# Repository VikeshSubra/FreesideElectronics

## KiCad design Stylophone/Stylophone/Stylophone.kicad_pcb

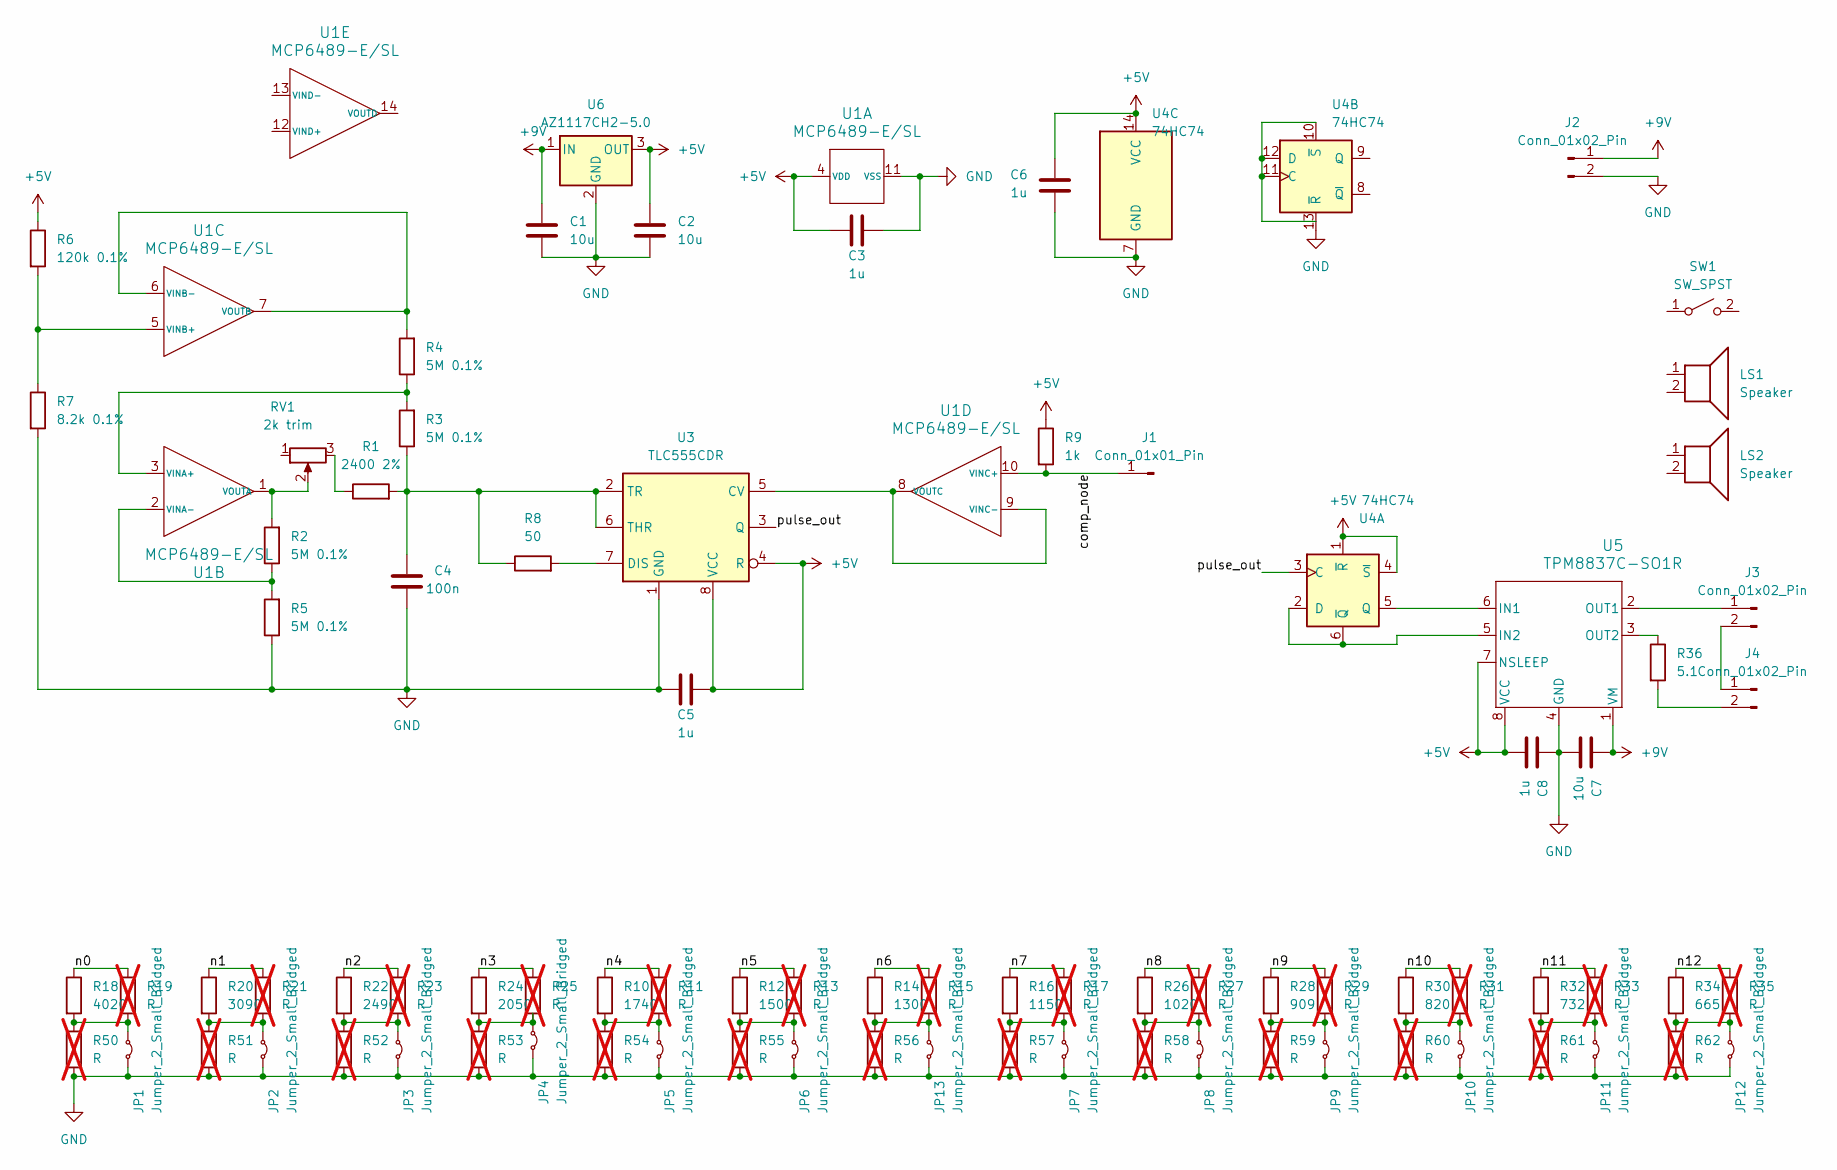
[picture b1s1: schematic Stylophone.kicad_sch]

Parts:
C1, C2, C7: 10u; C_1206_3216Metric; Part Number CL31B106KQHNFNE
C3, C5, C6, C8: 1u; C_1206_3216Metric; Part Number CL31B105KOFNNNE
C4: 100n; C_1206_3216Metric; Part Number GRM3195C1H104JA05D
J1: Conn_01x01_Pin; PinHeader_1x01_P2.54mm_Vertical
J2, J3, J4: Conn_01x02_Pin; PinHeader_1x02_P2.54mm_Vertical
JP1, JP2, JP3, JP4, JP5, JP6, JP7, JP8, JP9, JP10, JP11, JP12, JP13: Jumper_2_Small_Bridged; SolderJumper-2_P1.3mm_Bridged_RoundedPad1.0x1.5mm
LS1, LS2: Speaker; Part Number 687117740724
R1: 2400 2%; R_1206_3216Metric; Part Number RC1206FR-072K4L
R2, R3, R4, R5: 5M 0.1%; R_1206_3216Metric; Part Number RG3216P-5004-B-T1
R6: 120k 0.1%; R_1206_3216Metric; Part Number RT0805BRD07120KL
R7: 8.2k 0.1%; R_1206_3216Metric; Part Number RT0402BRD078K2L
R8: 50; R_1206_3216Metric; Part Number RC1206JR-0751RL
R9: 1k; R_1206_3216Metric
R10: 1740; R_1206_3216Metric; Part Number ERA-8AEB1741V
R11, R13, R15, R17, R19, R21, R23, R25, R27, R29, R31, R33, R35, R50, R51, R52, R53, R54, R55, R56, R57, R58, R59, R60, R61, R62: R; R_1206_3216Metric; not fitted
R12: 1500; R_1206_3216Metric; Part Number RT1206BRD071K5L
R14: 1300; R_1206_3216Metric; Part Number ERA-8AEB132V
R16: 1150; R_1206_3216Metric; Part Number RG3216P-1151-B-T5
R18: 4020; R_1206_3216Metric; Part Number ERA-8AEB4021V
R20: 3090; R_1206_3216Metric; Part Number ERA-8AEB3091V
R22: 2490; R_1206_3216Metric; Part Number RT1206BRD072K49L
R24: 2050; R_1206_3216Metric; Part Number RT1206BRD072K05L
R26: 1020; R_1206_3216Metric; Part Number ERA-8AEB1021V
R28: 909; R_1206_3216Metric; Part Number RT1206BRD07909RL
R30: 820; R_1206_3216Metric; Part Number ERA-8AEB821V
R32: 732; R_1206_3216Metric; Part Number ERA-8AEB7320V
R34: 665; R_1206_3216Metric; Part Number ERA-8AEB6650V
R36: 5.1; R_1225_3264Metric; Part Number LTR100JZPJ5R1
RV1: 2k trim; Potentiometer_Bourns_3314G_Vertical; Part Number 3314G-1-202E
SW1: SW_SPST; Part Number 016071636086
U1: MCP6489-E/SL; SOIC-14_3.9x8.7mm_P1.27mm; Part Number MCP6489-E/SL
U3: TLC555CDR; SOIC-8_3.9x4.9mm_P1.27mm; Part Number TLC555CDR
U4: 74HC74; SOIC-14_3.9x8.7mm_P1.27mm; Part Number SN74AC74DR
U5: TPM8837C-SO1R; SOIC-8_3.9x4.9mm_P1.27mm; Part Number TPM8837C-SO1R
U6: AZ1117CH2-5.0; SOT-223-3_TabPin2; Part Number AZ1117CH-5.0TRG1

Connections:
+5V: C2.1, C3.1, C5.2, C6.1, C8.2, R6.1, R9.1, U1.4 (VDD), U3.4 (R), U3.8 (VCC), U4.1 (~R), U4.4 (~S), U4.14 (VCC), U5.7 (NSLEEP), U5.8 (VCC), U6.3 (OUT)
+9V: C1.1, C7.1, J2.1, U5.1 (VM), U6.1 (IN)
/comp_node: J1.1, R9.2, U1.10 (VINC+)
/n0: R18.1, R19.1
/n1: R20.1, R21.1
/n2: R22.1, R23.1
/n3: R24.1, R25.1
/n4: R10.1, R11.1
/n5: R12.1, R13.1
/n6: R14.1, R15.1
/n7: R16.1, R17.1
/n8: R26.1, R27.1
/n9: R28.1, R29.1
/n10: R30.1, R31.1
/n11: R32.1, R33.1
/n12: R34.1, R35.1
/pulse_out: U3.3 (Q), U4.3 (C)
GND: C1.2, C2.2, C3.2, C4.1, C5.1, C6.2, C7.2, C8.1, J2.2, JP1.2 (B), JP2.2 (B), JP3.2 (B), JP4.2 (B), JP5.2 (B), JP6.2 (B), JP7.2 (B), JP8.2 (B), JP9.2 (B), JP10.2 (B), JP11.2 (B), JP12.2 (B), JP13.2 (B), R5.1, R7.2, R50.2, R51.2, R52.2, R53.2, R54.2, R55.2, R56.2, R57.2, R58.2, R59.2, R60.2, R61.2, R62.2, U1.11 (VSS), U3.1 (GND), U4.7 (GND), U4.13 (~R), U5.4 (GND), U6.2 (GND)
unnamed: J3.1, U5.2 (OUT1)
unnamed: J3.2, J4.1
unnamed: J4.2, R36.2
unnamed: JP1.1 (A), R18.2, R19.2, R50.1
unnamed: JP2.1 (A), R20.2, R21.2, R51.1
unnamed: JP3.1 (A), R22.2, R23.2, R52.1
unnamed: JP4.1 (A), R24.2, R25.2, R53.1
unnamed: JP5.1 (A), R10.2, R11.2, R54.1
unnamed: JP6.1 (A), R12.2, R13.2, R55.1
unnamed: JP7.1 (A), R16.2, R17.2, R57.1
unnamed: JP8.1 (A), R26.2, R27.2, R58.1
unnamed: JP9.1 (A), R28.2, R29.2, R59.1
unnamed: JP10.1 (A), R30.2, R31.2, R60.1
unnamed: JP11.1 (A), R32.2, R33.2, R61.1
unnamed: JP12.1 (A), R34.2, R35.2, R62.1
unnamed: JP13.1 (A), R14.2, R15.2, R56.1
unnamed: R1.1, RV1.3
unnamed: R3.2, R4.1, U1.3 (VINA+)
unnamed: R2.1, R5.2, U1.2 (VINA-)
unnamed: R2.2, RV1.2, U1.1 (VOUTA)
unnamed: R6.2, R7.1, U1.5 (VINB+)
unnamed: R4.2, U1.6 (VINB-), U1.7 (VOUTB)
unnamed: U1.8 (VOUTC), U1.9 (VINC-), U3.5 (CV)
unnamed: R8.2, U3.7 (DIS)
unnamed: C4.2, R1.2, R3.1, R8.1, U3.2 (TR), U3.6 (THR)
unnamed: U4.2 (D), U4.6 (~Q), U5.5 (IN2)
unnamed: U4.5 (Q), U5.6 (IN1)
unnamed: U4.10 (~S), U4.11 (C), U4.12 (D)
unnamed: R36.1, U5.3 (OUT2)

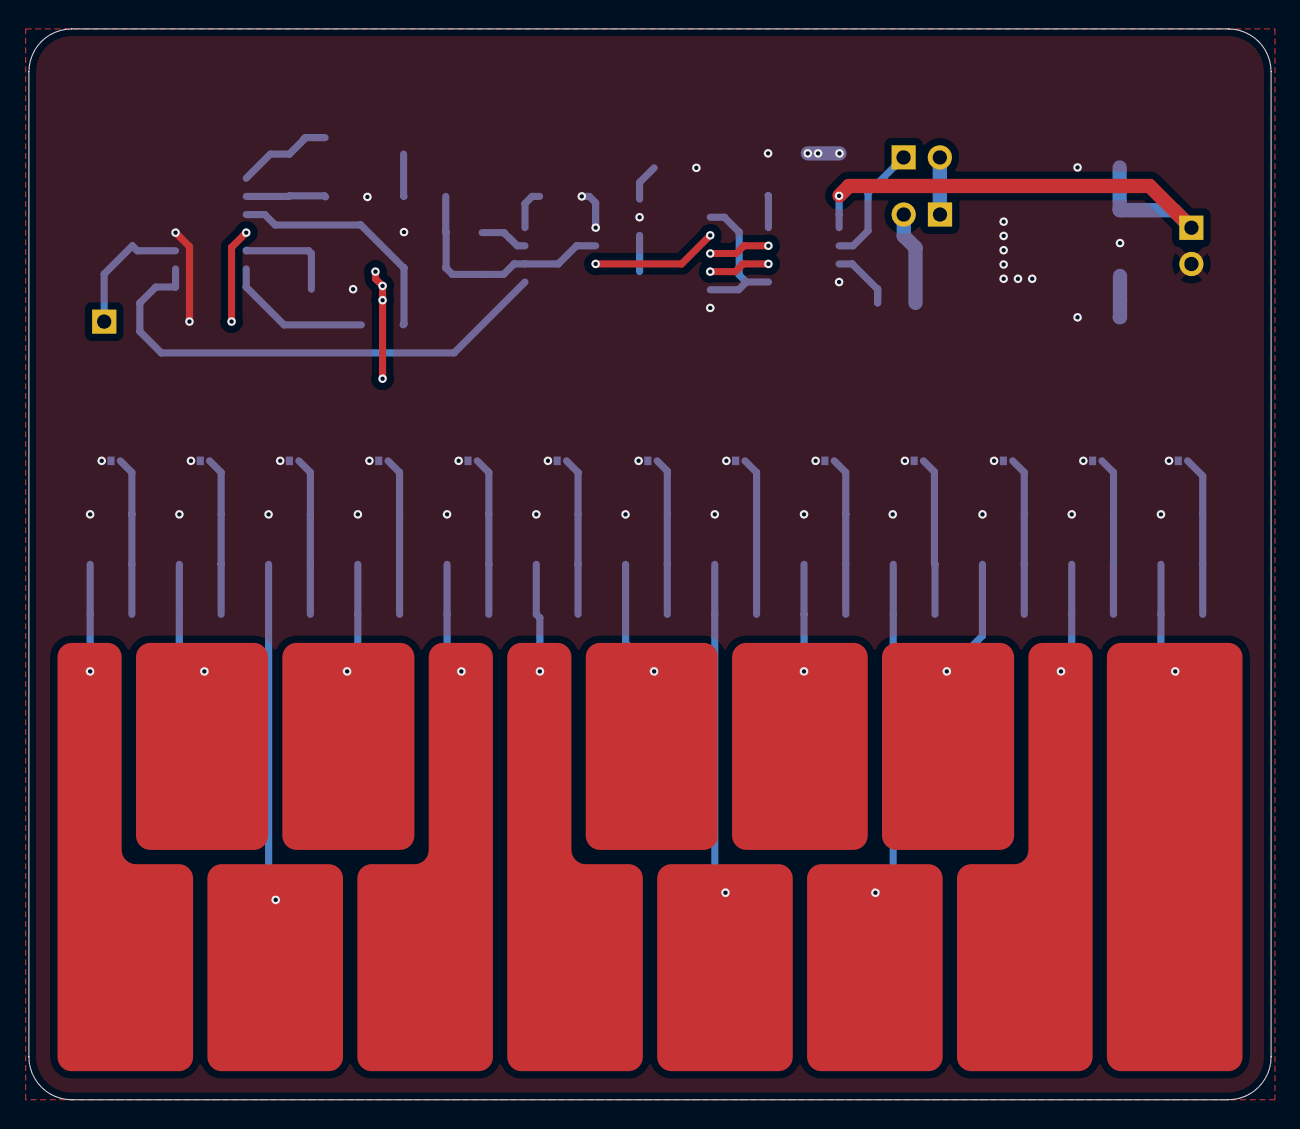
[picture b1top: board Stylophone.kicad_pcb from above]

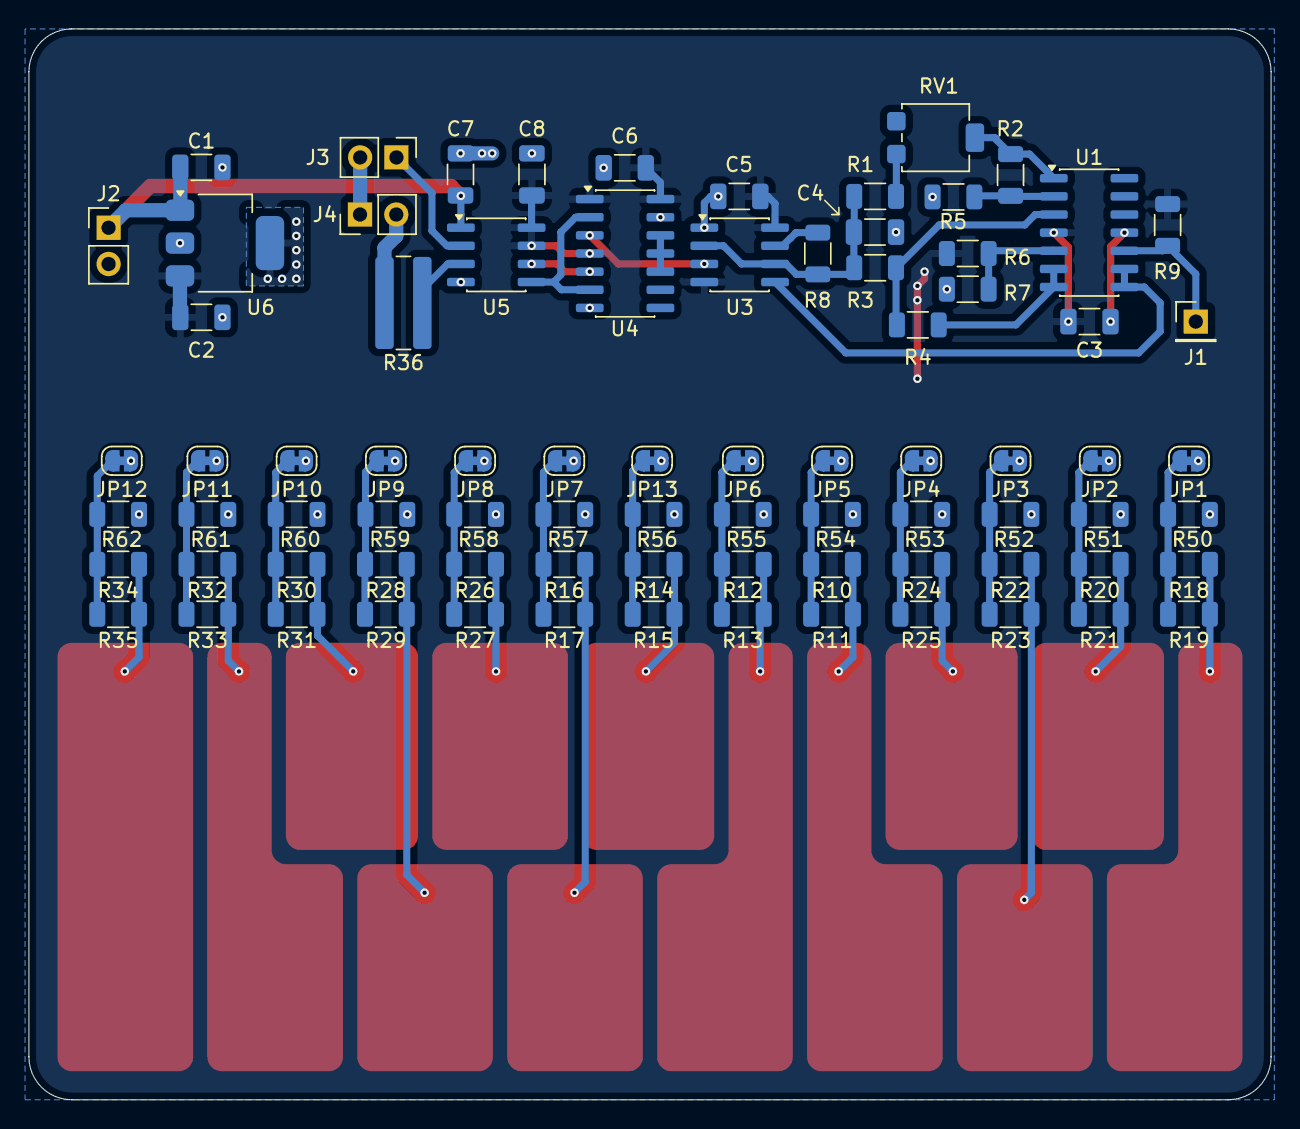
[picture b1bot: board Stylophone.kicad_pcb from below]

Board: 2 copper layers, 87.0 x 75.0 mm, 80 parts (80 on the bottom side), 47 nets.

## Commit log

2026-06-15 First Commit - Stylophone board for PCB class
